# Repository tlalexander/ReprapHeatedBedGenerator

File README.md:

Reprap Heated Bed Generator
===========================

Easily Generate EAGLE .brd files for a reprap heated bed.

This is a simple processing sketch that generates an eagle BRD file for eagle version 6+ for a reprap heated bed.

After you generate the board file, open it up, and press the "switch to schematic" button up top.

Eagle will generate a schematic that is linked to the board. Now you can add a power jack, a thermistor, LED, mounting holes - anything you want. For the power jack, connect both pins to "SIGNAL1" using the "name" command in Eagle. Switch to the board again, position your power connector, move the ends of the heater traces as needed, and add a trace that goes from one pin of the power jack to one end of the heater trace. Now connect the other pin of the jack to the other end of the heater trace, and do the same for the LED if needed. Throw on some text, some mounting holes, and voila!

This was tested to work with Processing 2.0 Alpha, and I think it uses an XML class that is different in 1.5.

Change values at the top of the sketch to mess with the board. If you want to get crazy, add a "target resistance" and find a way to calculate the optimum board for that. Or just keep making up numbers until you get close to what you want!

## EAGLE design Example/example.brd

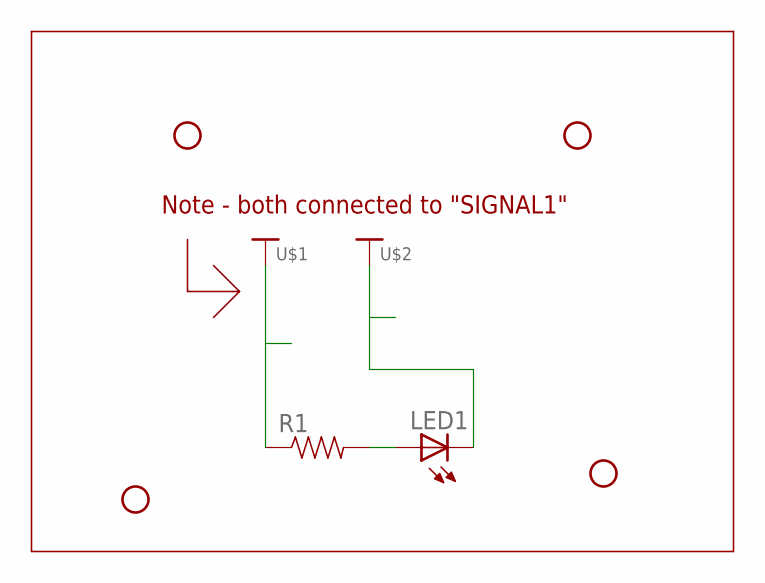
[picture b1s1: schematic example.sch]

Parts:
JP1, JP2, JP3, JP4: STAND-OFF
LED1: LED-FKIT-1206; FKIT-LED-1206
R1: RESISTOR0805-RES; 0805
U$1, U$2: HIGHCURRENTPAD2; HIGH_CURRENT_PAD2

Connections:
unnamed: LED1.A, R1.2
SIGNAL1: LED1.C, R1.1, U$1.P$1, U$2.P$1

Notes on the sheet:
Note - both connected to "SIGNAL1"

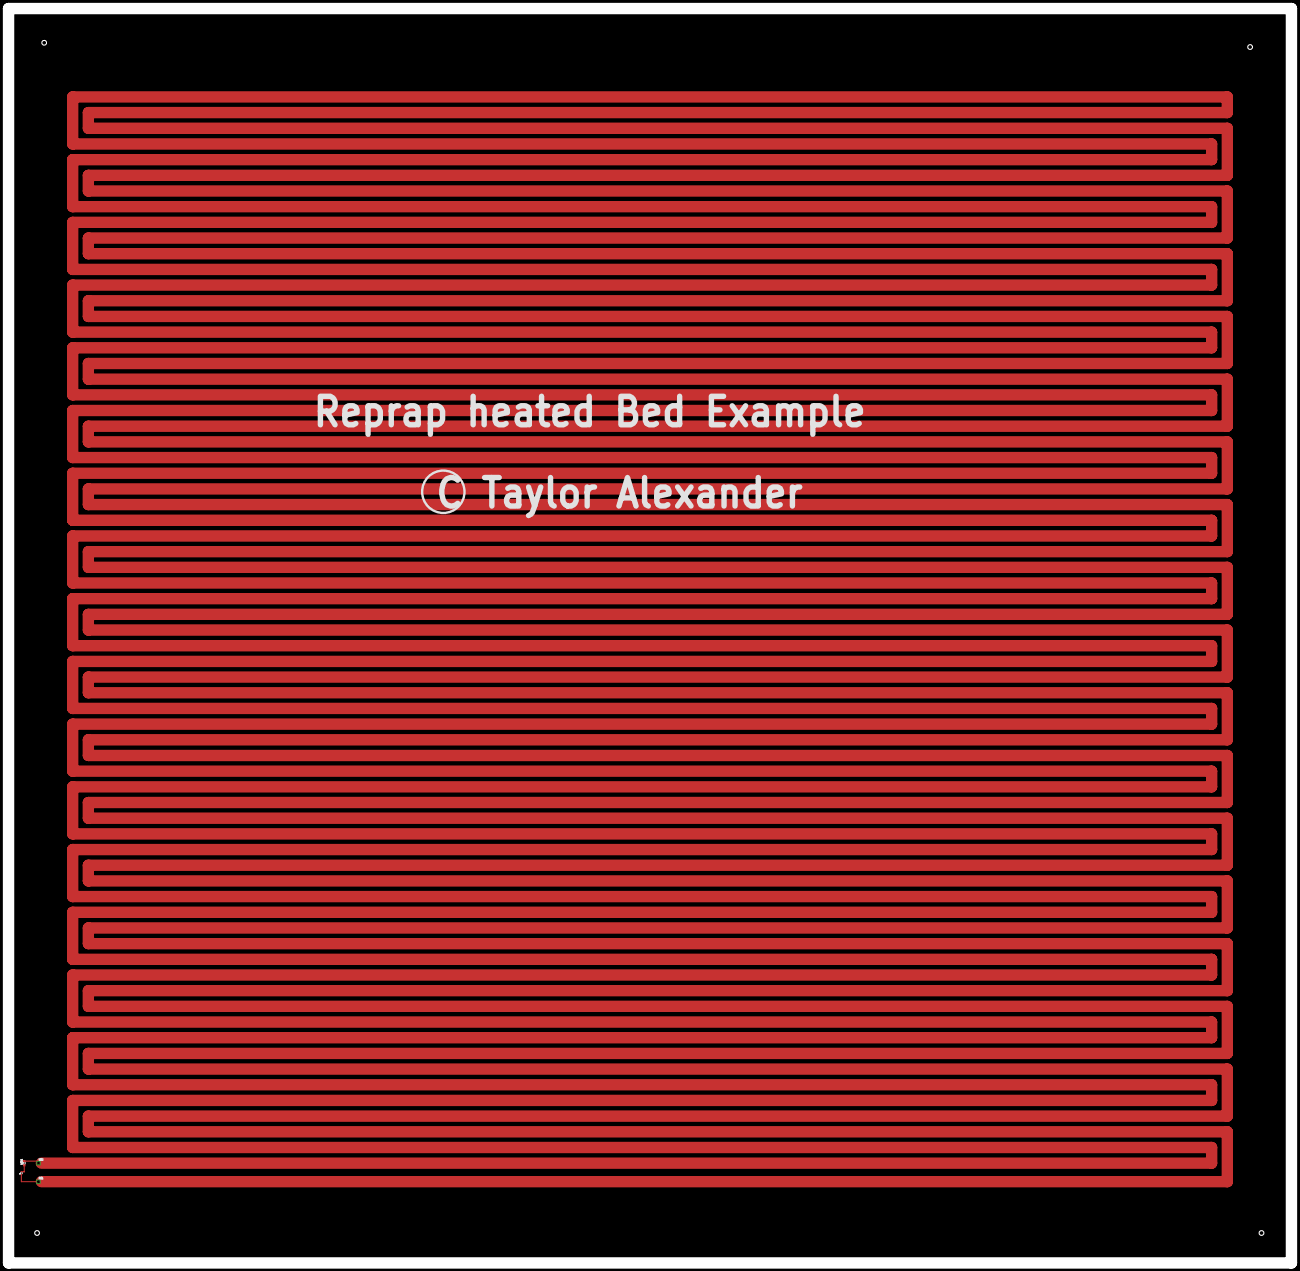
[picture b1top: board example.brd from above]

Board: 2 copper layers, 900.0 x 880.0 mm, 8 parts (0 on the bottom side), 2 nets.

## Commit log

2012-09-05 Add project files.
2012-10-25 Update xml.tostring for new versions of Processing
    they changed the .tostring() method. Just deleted the 2 and everything
    was good.

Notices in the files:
parts and their libraries:
SparkFun: Licensing: CC v3.0 Share-Alike You are welcome to use this library for commercial purposes.
